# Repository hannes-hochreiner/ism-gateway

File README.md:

# ism-gateway
A simple radio (434 MHz, ISM band) to USB gateway

## Firsts
The most exciting part of every project, are the things I have never done before.
This is a list of things that were new to me with this project:

  * USB (A/B micro connector, power and data)
  * RGB LEDs
  * LED controller with custom protocol
  * custom housing

## Housing
I had the housing laser cut from 2 mm plywood.
I assumed 0.1 mm of kerb, which worked fine for the most part.
The material seemed to be somewhat thicker than the advertised 2 mm or maybe just uneven.
Therefore, I had to file down side walls to make them fit into the holes of the top and bottom covers.
The cut-outs for the antenna, usb connector, LED, and threaded rods fit perfectly.
The case is held together by two threaded rods (M2) at opposite corners and fixed with nuts.
The rods also run through the mounting holes of the PCB.
Additional nuts are used to hold the PCB in place.

### Learnings
  * plywood cases look quite ok
  * 0.1 mm kerb is ok for 2 mm plywood
  * plywood is not necessarily exactly the nominal thickness
  * a metal file would be good to smooth the metal rod cut-faces

## Firmware
The firmware is based on code generated by the recommended STM tools.
I wrote custom drivers for the LED driver and the RFM98 module.
These drivers are able to operate in blocking or interrupt mode, depending on the functions provided by the calling code.

The LED driver is used in interrupt mode, currently.
The RFM98 is polled to check for newly received messages.

## Software
Any program that is able to read messages from generic CDC-ACM devices should be fine.
I wrote a small [monitoring program](https://github.com/hannes-hochreiner/usb-cdc-monitor) as a starting point.

### Ideas for improvement
  * the USB interrupts should be prioritized over the LED driver interrupts
  * interrupts should be used to check for received messages from the RFM98 module
  * USB messages should only be sent, if there is a receiver attached

## License
To all the parts that I developed, the MIT license applies.
Parts from third parties (e.g. generated code) may have other license restrictions.

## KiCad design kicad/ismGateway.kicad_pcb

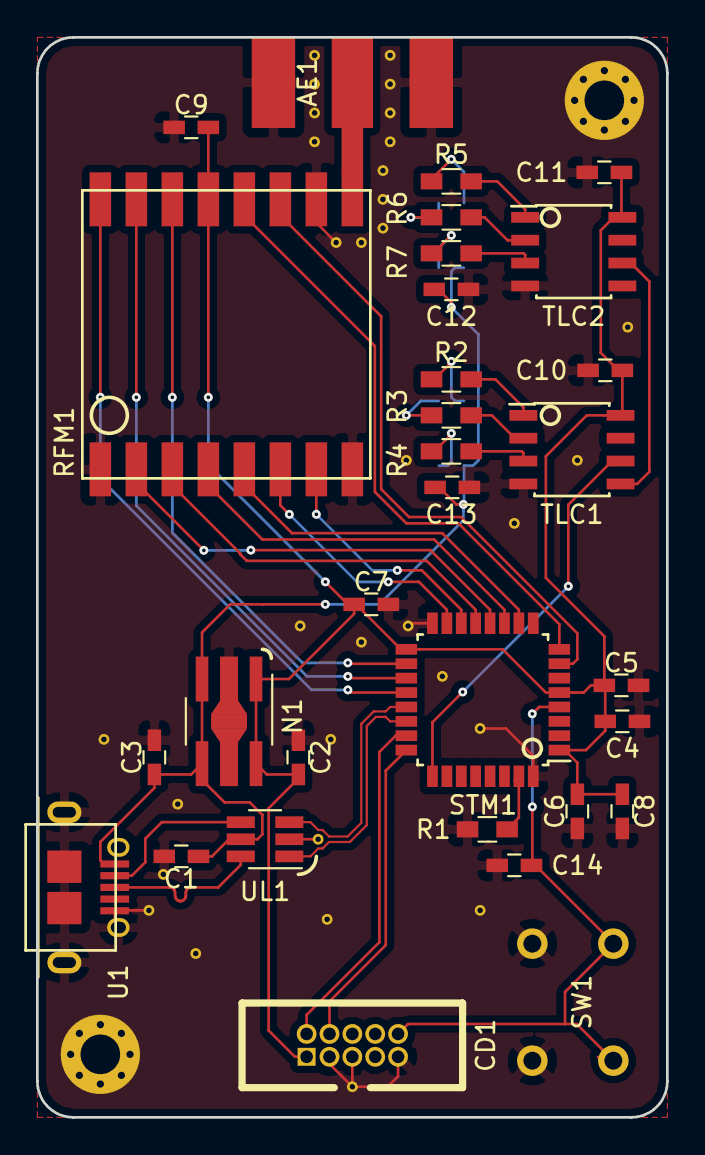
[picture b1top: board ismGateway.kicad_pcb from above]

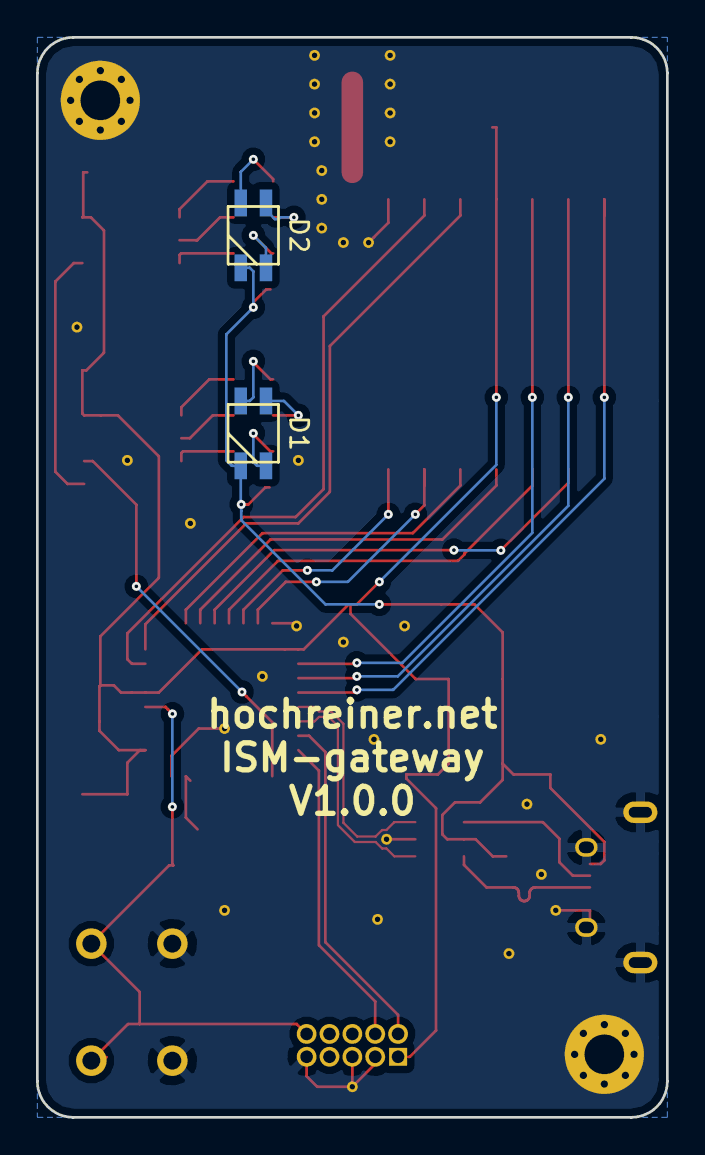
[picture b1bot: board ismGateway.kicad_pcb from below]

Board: 2 copper layers, 35.0 x 60.0 mm, 33 parts (2 on the bottom side), 37 nets.

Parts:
AE1: Antenna_Shield; MOLEX-0732511150
C1, C5, C6, C7, C9, C10, C11, C14: 0.1uF; C_0603_HandSoldering
C2, C3, C4: 1uF; C_0603_HandSoldering
C8, C12, C13: 10uF; C_0603_HandSoldering
CD1: CORTEX-DEBUG
D1, D2: LED_ARGB; CreePLCC4
N1: NCP4687-SOT-89; SOT89-5_Housing_Handsoldering
R1: 10k; R_0603_HandSoldering
R2, R3, R5, R6: 130; R_0603_HandSoldering
R4, R7: 150; R_0603_HandSoldering
RFM1: RFM98
STM1: STM32L062K8T6; LQFP-32_7x7mm_Pitch0.8mm
SW1: SW_Push; switch
TLC1, TLC2: TLC59731; SOIC-8_3.9x4.9mm_Pitch1.27mm
U1: USB_micro_ab; MOLEX_USB_MICRO_0475890001
UL1: USBLC6-2; SOT-23-6_Handsoldering

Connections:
/3V3: C2.2, C4.1, C5.1, C6.2, C7.1, C8.1, C9.2, C10.2, C11.2, CD1.1, N1.1, N1.5, RFM1.13, STM1.1, STM1.5, STM1.17, TLC1.8, TLC2.8
/LED_SDI: STM1.25, TLC1.6
/RFM_IO0: RFM1.14, STM1.18
/RFM_IO1: RFM1.15, STM1.19
/RFM_IO2: RFM1.16, STM1.20
/RFM_IO3: RFM1.11, STM1.7
/RFM_IO4: RFM1.12, STM1.8
/RFM_IO5: RFM1.7, STM1.14
/RFM_RESET: RFM1.6, STM1.15
/SPI_MISO: RFM1.2, STM1.12
/SPI_MOSI: RFM1.3, STM1.13
/SPI_NSS: RFM1.5, STM1.10
/SPI_SCK: RFM1.4, STM1.11
/SWCLK: CD1.4, STM1.24
/SWDIO: CD1.2, STM1.23
/SWD_NRST: C14.1, CD1.10, STM1.4, SW1.2
/USB_D+: STM1.22, UL1.1
/USB_D-: STM1.21, UL1.3
/VBUS: C1.1, C3.1, C12.1, C13.1, D1.1, D2.1, N1.3, N1.4, U1.1, UL1.5
GND: AE1.2, C1.2, C2.1, C3.2, C4.2, C5.2, C6.1, C7.2, C8.2, C9.1, C10.1, C11.1, C12.2, C13.2, C14.2, CD1.3, CD1.5, CD1.9, N1.2, R1.2, RFM1.1, RFM1.8, RFM1.10, STM1.16, STM1.32, SW1.1, TLC1.4, TLC2.4, U1.5, UL1.2
unnamed: AE1.1, RFM1.9
unnamed: D1.2, R4.2
unnamed: D1.3, R3.2
unnamed: D1.4, R2.2
unnamed: D2.2, R7.2
unnamed: D2.3, R6.2
unnamed: D2.4, R5.2
unnamed: R1.1, STM1.31
unnamed: R2.1, TLC1.1
unnamed: R3.1, TLC1.2
unnamed: R4.1, TLC1.3
unnamed: R5.1, TLC2.1
unnamed: R6.1, TLC2.2
unnamed: R7.1, TLC2.3
unnamed: TLC1.5, TLC2.6
unnamed: U1.2, UL1.4
unnamed: U1.3, UL1.6

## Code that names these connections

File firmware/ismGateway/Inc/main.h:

/**
  ******************************************************************************
  * @file           : main.h
  * @brief          : Header for main.c file.
  *                   This file contains the common defines of the application.
  ******************************************************************************
  * This notice applies to any and all portions of this file
  * that are not between comment pairs USER CODE BEGIN and
  * USER CODE END. Other portions of this file, whether 
  * inserted by the user or by software development tools
  * are owned by their respective copyright owners.
  *
  * Copyright (c) 2018 STMicroelectronics International N.V. 
  * All rights reserved.
  *
  * Redistribution and use in source and binary forms, with or without 
  * modification, are permitted, provided that the following conditions are met:
  *
  * 1. Redistribution of source code must retain the above copyright notice, 
  *    this list of conditions and the following disclaimer.
  * 2. Redistributions in binary form must reproduce the above copyright notice,
  *    this list of conditions and the following disclaimer in the documentation
  *    and/or other materials provided with the distribution.
  * 3. Neither the name of STMicroelectronics nor the names of other 
  *    contributors to this software may be used to endorse or promote products 
  *    derived from this software without specific written permission.
  * 4. This software, including modifications and/or derivative works of this 
  *    software, must execute solely and exclusively on microcontroller or
  *    microprocessor devices manufactured by or for STMicroelectronics.
  * 5. Redistribution and use of this software other than as permitted under 
  *    this license is void and will automatically terminate your rights under 
  *    this license. 
  *
  * THIS SOFTWARE IS PROVIDED BY STMICROELECTRONICS AND CONTRIBUTORS "AS IS" 
  * AND ANY EXPRESS, IMPLIED OR STATUTORY WARRANTIES, INCLUDING, BUT NOT 
  * LIMITED TO, THE IMPLIED WARRANTIES OF MERCHANTABILITY, FITNESS FOR A 
  * PARTICULAR PURPOSE AND NON-INFRINGEMENT OF THIRD PARTY INTELLECTUAL PROPERTY
  * RIGHTS ARE DISCLAIMED TO THE FULLEST EXTENT PERMITTED BY LAW. IN NO EVENT 
  * SHALL STMICROELECTRONICS OR CONTRIBUTORS BE LIABLE FOR ANY DIRECT, INDIRECT,
  * INCIDENTAL, SPECIAL, EXEMPLARY, OR CONSEQUENTIAL DAMAGES (INCLUDING, BUT NOT
  * LIMITED TO, PROCUREMENT OF SUBSTITUTE GOODS OR SERVICES; LOSS OF USE, DATA, 
  * OR PROFITS; OR BUSINESS INTERRUPTION) HOWEVER CAUSED AND ON ANY THEORY OF 
  * LIABILITY, WHETHER IN CONTRACT, STRICT LIABILITY, OR TORT (INCLUDING 
  * NEGLIGENCE OR OTHERWISE) ARISING IN ANY WAY OUT OF THE USE OF THIS SOFTWARE,
  * EVEN IF ADVISED OF THE POSSIBILITY OF SUCH DAMAGE.
  *
  ******************************************************************************
  */

/* Define to prevent recursive inclusion -------------------------------------*/
#ifndef __MAIN_H__
#define __MAIN_H__

/* Includes ------------------------------------------------------------------*/
#include "stm32l0xx_ll_crs.h"
#include "stm32l0xx_ll_rcc.h"
#include "stm32l0xx_ll_bus.h"
#include "stm32l0xx_ll_system.h"
#include "stm32l0xx_ll_exti.h"
#include "stm32l0xx_ll_cortex.h"
#include "stm32l0xx_ll_utils.h"
#include "stm32l0xx_ll_pwr.h"
#include "stm32l0xx_ll_dma.h"
#include "stm32l0xx_ll_spi.h"
#include "stm32l0xx_ll_tim.h"
#include "stm32l0xx.h"
#include "stm32l0xx_ll_gpio.h"

/* USER CODE BEGIN Includes */
#include "tlc59731.h"
/* USER CODE END Includes */

/* Private define ------------------------------------------------------------*/

#define SPI1_NSS_Pin LL_GPIO_PIN_4
#define SPI1_NSS_GPIO_Port GPIOA
#define RFM_RESET_Pin LL_GPIO_PIN_1
#define RFM_RESET_GPIO_Port GPIOB
#define RFM_IO0_Pin LL_GPIO_PIN_8
#define RFM_IO0_GPIO_Port GPIOA
#define RFM_IO0_EXTI_IRQn EXTI4_15_IRQn
#define LED_SDI_Pin LL_GPIO_PIN_15
#define LED_SDI_GPIO_Port GPIOA

/* ########################## Assert Selection ############################## */
/**
  * @brief Uncomment the line below to expanse the "assert_param" macro in the 
  *        HAL drivers code
  */
/* #define USE_FULL_ASSERT    1U */

/* USER CODE BEGIN Private defines */
void TIMER_Callback();
void led_delay();
void led_set_pin();
void led_reset_pin();
void ReadData(int16_t rssi, const uint8_t* const data, uint8_t length);
void SetColors(const bitbang_calls_t* const calls, const color_t* const, const color_t* const);
void EXTI_Callback();
/* USER CODE END Private defines */

#ifdef __cplusplus
 extern "C" {
#endif
void _Error_Handler(char *, int);

#define Error_Handler() _Error_Handler(__FILE__, __LINE__)
#ifdef __cplusplus
}
#endif

#endif /* __MAIN_H__ */

/************************ (C) COPYRIGHT STMicroelectronics *****END OF FILE****/

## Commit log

2018-04-24 added firsts
2018-04-24 added image
2018-04-24 added kicad files
2018-04-28 added housing
2018-04-28 updated images
2018-05-01 refactored README
2018-05-01 added firmware
2018-08-22 added debug target
2018-08-26 added note about software
2018-08-26 added c properties
2018-08-26 updated cube version
2018-08-26 switched to using interrupts from rfm module
2018-08-26 refactored LED functions
2018-08-26 based radio state check on pin state
2018-09-08 added rfm library as a submodule
2018-09-08 update rfm library
2018-10-03 setting crc autoclear mode
2018-10-03 added setting of frequency deviation
2018-10-03 updated submodule
2018-10-04 updated rfm library
2018-11-10 started work on driver
2018-11-10 added device iteration
2018-11-11 added reading of values
2018-11-11 improved error handling
2018-11-13 added interpretation of messages
2018-11-13 fixed bug
2018-11-13 fixed conversion to percentage
2018-11-25 updated hoperf library
2018-11-25 snapshot
2018-12-29 removed dead code and added an rfm reset
2018-12-29 switch to memcpy
2019-01-01 switched from rust to c++
2019-01-03 added decryption
2019-01-04 added zeromq publishing
2019-01-04 added description of crypto++
2019-01-06 improved makefile and error reporting
2019-01-21 switched to LoRa
2019-01-21 fixed a wrong pointer
2019-01-21 fixed the message length
2019-01-21 added second message
2019-01-22 switched to reporting unexpected lengths
2019-01-25 added crc flag check
